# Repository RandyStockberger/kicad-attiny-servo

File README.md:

# kicad-attiny-servo
KiCad files for an attiny4313 model railroad turnout controller driven by servos

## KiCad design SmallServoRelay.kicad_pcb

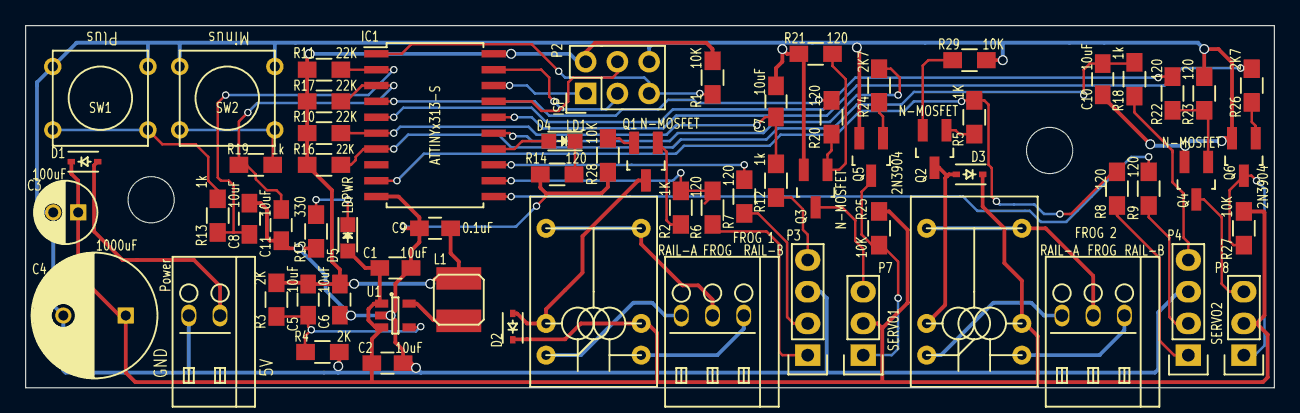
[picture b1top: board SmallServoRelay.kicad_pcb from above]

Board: 2 copper layers, 100.0 x 29.0 mm, 66 parts (0 on the bottom side), 53 nets.

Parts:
C1, C2, C5, C6, C7, C8, C10, C11: 10uF; C_0805_HandSoldering
C3: 100uF; C_Radial_D5_L11_P2
C4: 1000uF; C_Radial_D10_L16_P5
C9: 0.1uF; C_0805_HandSoldering
D1: Diode; SOD-323
D2, D3: Schottky; SOD-323
D4: LD1; LED_0805
D5: LDPWR; LED_0805
IC1: ATTINYx313-S; SOIC-20_7.5x12.8mm_Pitch1.27mm
L1: INDUCTOR; Bourns-Inductor-SRN4026
P1: Power; Phoenix-Combicon-2.5mm-2
P2: ISP; Pin_Header_Straight_2x03
P3, P4: CONN_01X04; Pin_Header_Straight_1x04
P5: FROG 1; Phoenix-Combicon-2.5mm-3
P6: FROG 2; Phoenix-Combicon-2.5mm-3
P7: SERVO1; Pin_Header_Straight_1x03
P8: SERVO2; Pin_Header_Straight_1x03
Q1, Q2, Q3, Q4: N-MOSFET; SOT-23_Handsoldering
Q5, Q6: 2N3904; SOT-23_Handsoldering
R1, R25, R27, R28, R29: 10K; R_0805_HandSoldering
R2, R5: 1K; R_0805_HandSoldering
R3, R4: 2K; R_0805_HandSoldering
R6, R7, R8, R9, R14, R20, R21, R22, R23: 120; R_0805_HandSoldering
R10, R11, R16, R17: 22K; R_0805_HandSoldering
R12, R13, R18, R19: 1k; R_0805_HandSoldering
R15: 330; R_0805_HandSoldering
R24, R26: 2K7; R_0805_HandSoldering
RLY1, RLY2: SPDT; Relay_SPDT-Form_C
SW1: BTN-PLUS; SW_PUSH_SMALL
SW2: BTN-MINUS; SW_PUSH_SMALL
U1: PAM2305DABADJ; SOT-23-5

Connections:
+3V3: C5.1, C6.1, C9.1, IC1.20, L1.2, P2.2, R1.2, R3.2, R10.1, R11.1, R16.1, R17.1
+5V: C1.1, C2.1, C3.1, C4.1, D1.1, D2.1, D3.1, D5.2, P7.2, P8.2, R25.2, R27.2, RLY1.2, RLY2.2, U1.1, U1.3
/BTMINUS: C11.1, IC1.3, R17.2, R19.2
/BTPLUS: C8.1, IC1.2, R11.2, R13.2
/BTS1: C7.1, IC1.6, R10.2, R12.2
/BTS2: C10.1, IC1.7, R16.2, R18.2
/CBT1: P3.4, R12.1
/CBT2: P4.4, R18.1
/FROG1: P5.2, RLY1.5, RLY1.6
/FROG2: P6.2, RLY2.5, RLY2.6
/LD1A: IC1.12, R2.2, R6.2
/LD1B: IC1.13, R7.2
/LD2A: IC1.9, R5.2, R8.2
/LD2B: IC1.11, R9.2
/LED1: D4.2, IC1.14
/MISO: IC1.18, P2.1
/MOSI: IC1.17, P2.4
/RAIL-A1: P5.1, RLY1.1
/RAIL-A2: P6.1, RLY2.1
/RAIL-B1: P5.3, RLY1.10
/RAIL-B2: P6.3, RLY2.10
/SCK: IC1.19, P2.3
/SV1: IC1.15, R24.2
/SV1EN: IC1.4, R20.2
/SV1GND: P7.3, Q3.3
/SV1SIG: P7.1, Q5.3, R25.1
/SV2: IC1.16, R26.2
/SV2EN: IC1.5, R22.2
/SV2GND: P8.3, Q4.3
/SV2SIG: P8.1, Q6.3, R27.1
/~RESET: IC1.1, P2.5, R1.1
GND: C1.2, C2.2, C3.2, C4.2, C6.2, C7.2, C8.2, C9.2, C10.2, C11.2, IC1.10, P1.2, P2.6, P3.3, P4.3, Q3.2, Q4.2, Q5.2, Q6.2, R4.1, R14.2, R15.2, R21.1, R23.1, R28.1, R29.1, SW1.2, SW2.2, U1.2
unnamed: C5.2, R3.1, R4.2, U1.4
unnamed: D1.2, P1.1
unnamed: D2.2, Q1.3, RLY1.9
unnamed: D3.2, Q2.3, RLY2.9
unnamed: D4.1, R14.1
unnamed: D5.1, R15.1
unnamed: L1.1, U1.5
unnamed: P3.1, R6.1
unnamed: P3.2, R7.1
unnamed: P4.1, R8.1
unnamed: P4.2, R9.1
unnamed: Q1.1, R2.1
unnamed: Q1.2, R28.2
unnamed: Q2.1, R5.1
unnamed: Q2.2, R29.2
unnamed: Q3.1, R20.1, R21.2
unnamed: Q4.1, R22.1, R23.2
unnamed: Q5.1, R24.1
unnamed: Q6.1, R26.1
unnamed: R13.1, SW1.1
unnamed: R19.1, SW2.1

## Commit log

2017-01-31 Created repo for KiCad files used by the ATTiny4313 Servo driver with relays to control the Frogs

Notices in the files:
SmallServoRelay.kicad_pcb:
Copyright 2016, Randy Stockberger
